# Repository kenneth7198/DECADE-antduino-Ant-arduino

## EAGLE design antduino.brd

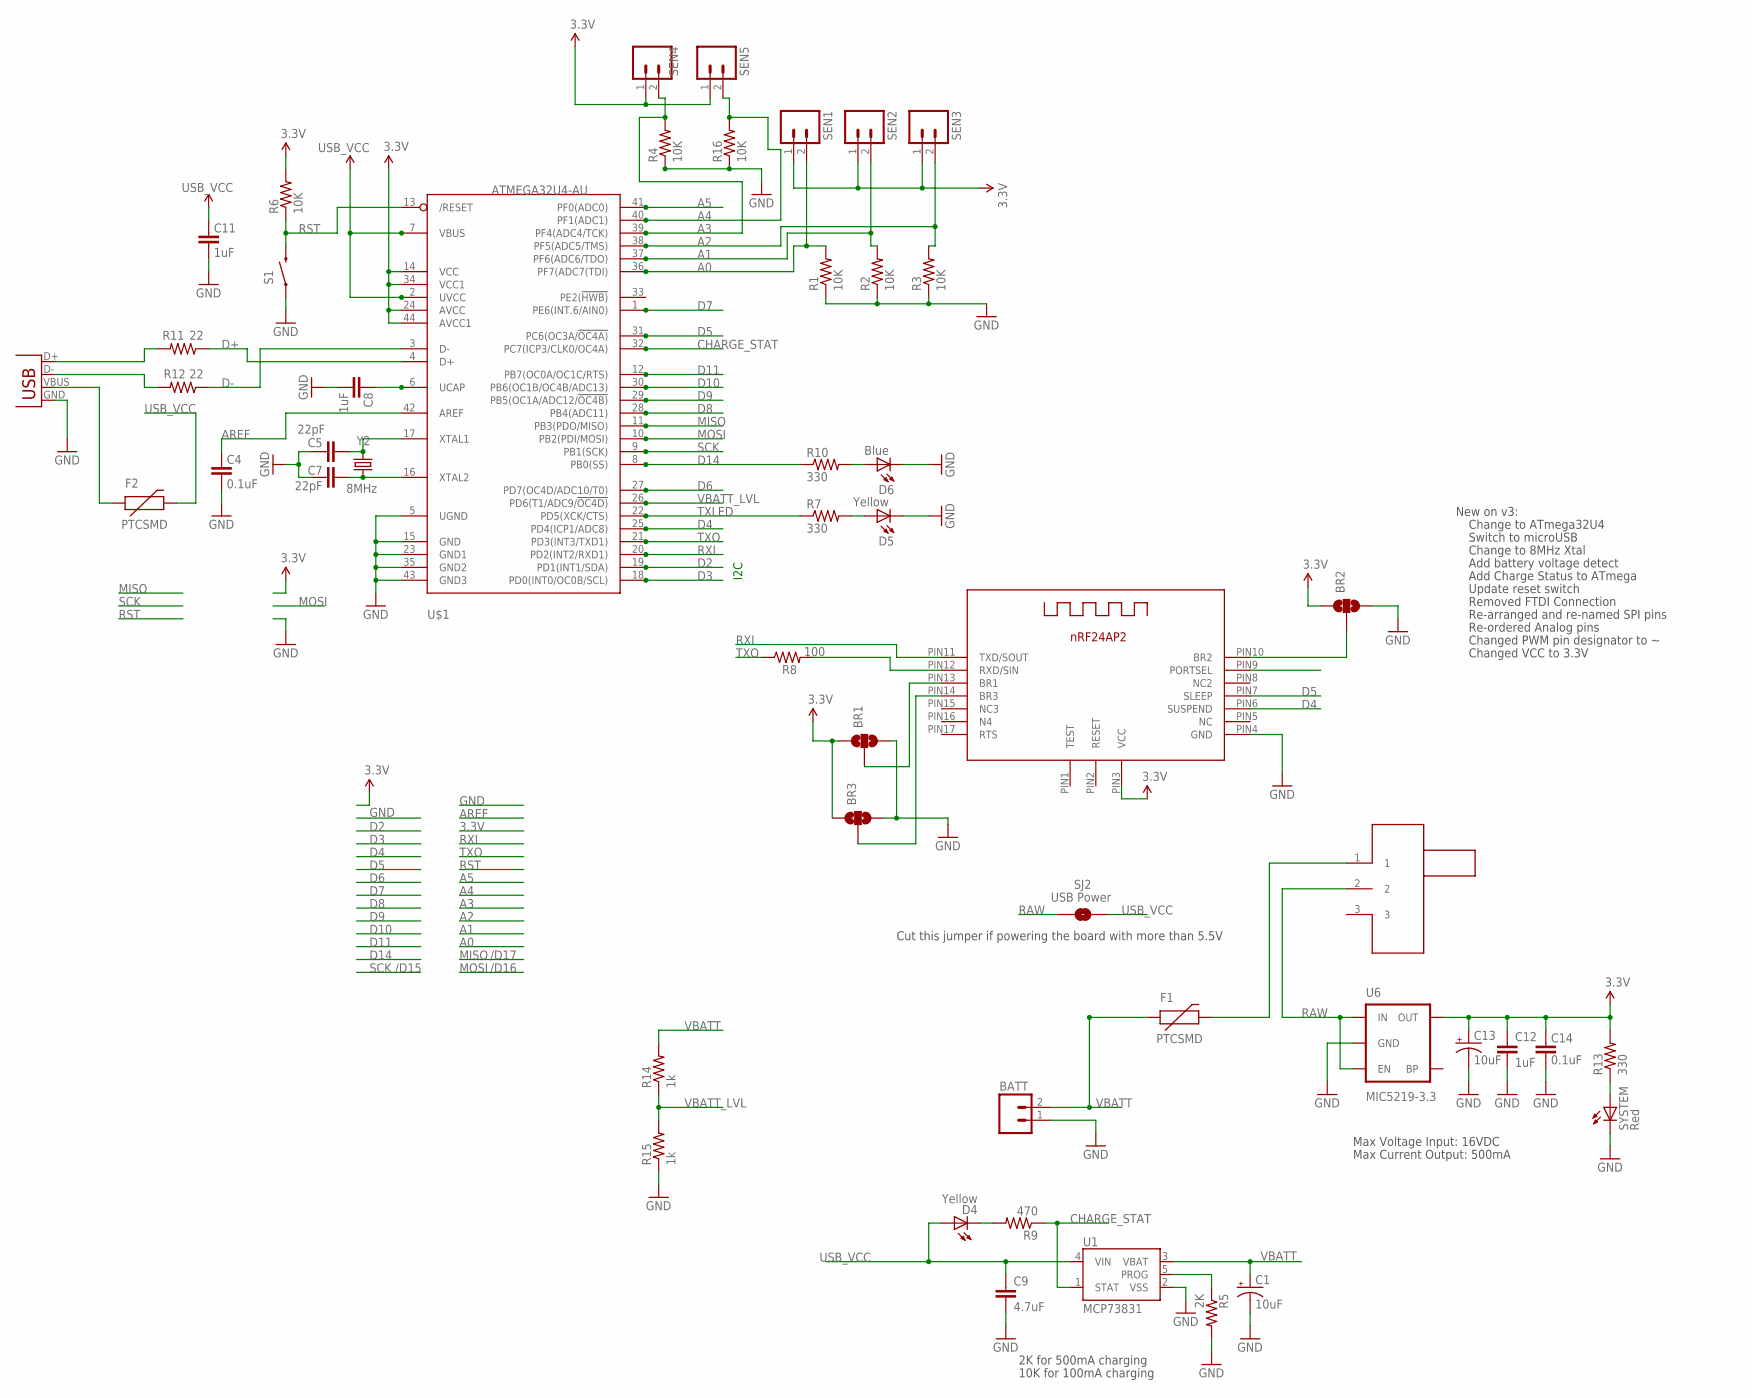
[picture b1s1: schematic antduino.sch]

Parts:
BATT: M02PTH; 1X02
BR1, BR2, BR3: SOLDERJUMPER_2WAY-OLDS; SJ_3
C1, C13: 10uF; EIA3216
C4, C14: 0.1uF; 0402-CAP
C5, C7: 22pF; 0402-CAP
C8, C11, C12: 1uF; 0402-CAP
C9: 4.7uF; 0402-CAP
D4, D5: Yellow; LED-0603
D6: Blue; LED-0603
F1, F2: PTCSMD; PTC-1206
R1, R2, R3, R4, R6, R16: 10K; 0402-RES
R5: 2K; 0402-RES
R7, R10, R13: 330; 0402-RES
R8: 100; 0402-RES
R9: 470; 0402-RES
R11, R12: 22; 0402-RES
R14, R15: 1k; 0402-RES
S1: SWITCH-MOMENTARY-2-SMD-1101NE; TACTILE-SWITCH-1101NE
SEN1, SEN2, SEN3: M02-JST-2MM-SMT; JST-2-SMD
SEN4, SEN5: M02PTH; 1X02
SJ2: USB Power; SJ_2S-TRACE
SYSTEM: Red; LED-0603
U1: MCP73831; SOT23-5
U6: MIC5219-3.3; SOT23-5
U$1: ATMEGA32U4-AU; TQFP44
U$2: DECADE-NRF24AP2-PCB-ANT; DECADE-NRF24AP2-PCB
U$4: DECADE-SW-SMALL; DECADE-SW-SM
X2: USB-MICROB
Y2: 8MHz; CRYSTAL-SMD-5X3

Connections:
3.3V: BR1.1, BR2.1, BR3.1, C12.1, C13.A (+), C14.2, R6.2, R13.2, SEN1.1, SEN2.1, SEN3.1, SEN4.1, SEN5.1, U6.5 (OUT), U$1.14 (VCC), U$1.24 (AVCC), U$1.34 (VCC1), U$1.44 (AVCC1), U$2.PIN3 (VCC)
A0: R1.2, SEN1.2, U$1.36 (PF7(ADC7(TDI))
A1: R2.2, SEN2.2, U$1.37 (PF6(ADC6/TDO))
A2: R3.2, SEN3.2, U$1.38 (PF5(ADC5/TMS))
A3: R4.2, SEN4.2, U$1.39 (PF4(ADC4/TCK))
A4: R16.2, SEN5.2, U$1.40 (PF1(ADC1))
A5: U$1.41 (PF0(ADC0))
AREF: C4.2, U$1.42 (AREF)
CHARGE_STAT: R9.1, U1.1 (STAT), U$1.32 (PC7(ICP3/CLK0/OC4A))
D2: U$1.19 (PD1(INT1/SDA))
D3: U$1.18 (PD0(INT0/OC0B/SCL))
D4: U$1.25 (PD4(ICP1/ADC8)), U$2.PIN6 (SUSPEND)
D5: U$1.31 (PC6(OC3A/!OC4A)), U$2.PIN7 (SLEEP)
D6: U$1.27 (PD7(OC4D/ADC10/T0))
D7: U$1.1 (PE6(INT.6/AIN0))
D8: U$1.28 (PB4(ADC11))
D9: U$1.29 (PB5(OC1A/ADC12/!OC4B))
D10: U$1.30 (PB6(OC1B/OC4B/ADC13))
D11: U$1.12 (PB7(OC0A/OC1C/RTS))
D14: R10.1, U$1.8 (PB0(SS))
D+: R11.1, U$1.4 (D+)
D-: R12.1, U$1.3 (D-)
GND: BATT.1, BR1.3, BR2.3, BR3.3, C1.C (-), C4.1, C5.2, C7.2, C8.1, C9.2, C11.1, C12.2, C13.C (-), C14.1, D5.C, D6.C, R1.1, R2.1, R3.1, R4.1, R5.2, R15.1, R16.1, S1.P$1 (1), SYSTEM.C, U1.2 (VSS), U6.2 (GND), U$1.5 (UGND), U$1.15 (GND), U$1.23 (GND1), U$1.35 (GND2), U$1.43 (GND3), U$2.PIN4 (GND), X2.GND
MISO: U$1.11 (PB3(PDO/MISO))
MOSI: U$1.10 (PB2(PDI/MOSI))
unnamed: F2.1, X2.VBUS
unnamed: BR2.2, U$2.PIN10 (BR2)
unnamed: BR1.2, U$2.PIN13 (BR1)
unnamed: BR3.2, U$2.PIN14 (BR3)
unnamed: R8.2, U$2.PIN12 (RXD/SIN)
unnamed: D4.C, R9.2
unnamed: F1.2, U$4.1
unnamed: R5.1, U1.5 (PROG)
unnamed: D5.A, R7.2
unnamed: C7.1, U$1.16 (XTAL2), Y2.1
unnamed: C5.1, U$1.17 (XTAL1), Y2.3 (2)
unnamed: D6.A, R10.2
unnamed: R12.2, X2.D-
unnamed: R11.2, X2.D+
unnamed: R13.1, SYSTEM.A
RAW: SJ2.1, U6.1 (IN), U6.3 (EN), U$4.2
RST: R6.1, S1.P$2 (2), U$1.13 (/RESET)
RXI: U$1.20 (PD2(INT2/RXD1)), U$2.PIN11 (TXD/SOUT)
SCK: U$1.9 (PB1(SCK))
TXLED: R7.1, U$1.22 (PD5(XCK/CTS))
TXO: R8.1, U$1.21 (PD3(INT3/TXD1))
UCAP: C8.2, U$1.6 (UCAP)
USB_VCC: C9.1, C11.2, D4.A, F2.2, SJ2.2, U1.4 (VIN), U$1.2 (UVCC), U$1.7 (VBUS)
VBATT: BATT.2, C1.A (+), F1.1, R14.2, U1.3 (VBAT)
VBATT_LVL: R14.1, R15.2, U$1.26 (PD6(T1/ADC9/!OC4D))

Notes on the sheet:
/D16
/D17
/D15
Change to ATmega32U4
Switch to microUSB
New on v3:
Change to 8MHz Xtal
Max Voltage Input: 16VDC
Max Current Output: 500mA
Cut this jumper if powering the board with more than 5.5V
2K for 500mA charging
10K for 100mA charging
Add battery voltage detect
Add Charge Status to ATmega
Update reset switch
Removed FTDI Connection
Re-arranged and re-named SPI pins
Re-ordered Analog pins
Changed PWM pin designator to ~
Changed VCC to 3.3V
I2C

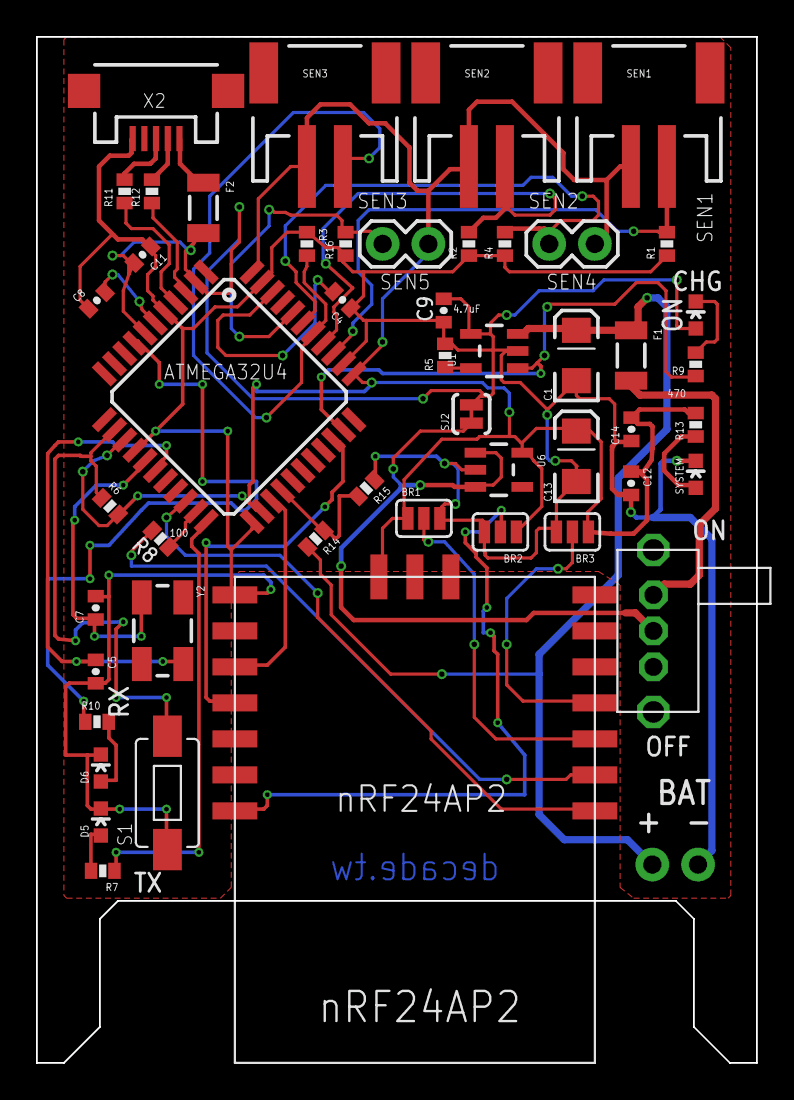
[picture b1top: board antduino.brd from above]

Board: 2 copper layers, 40.0 x 57.0 mm, 50 parts (1 on the bottom side), 38 nets.

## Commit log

2013-04-16 ANT+ and Arduino Leonardo
    ANT+ and Arduino Leonardo

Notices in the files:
parts and their libraries:
SparkFun-Passives: Licensing: CC v3.0 Share-Alike You are welcome to use this library for commercial purposes.
